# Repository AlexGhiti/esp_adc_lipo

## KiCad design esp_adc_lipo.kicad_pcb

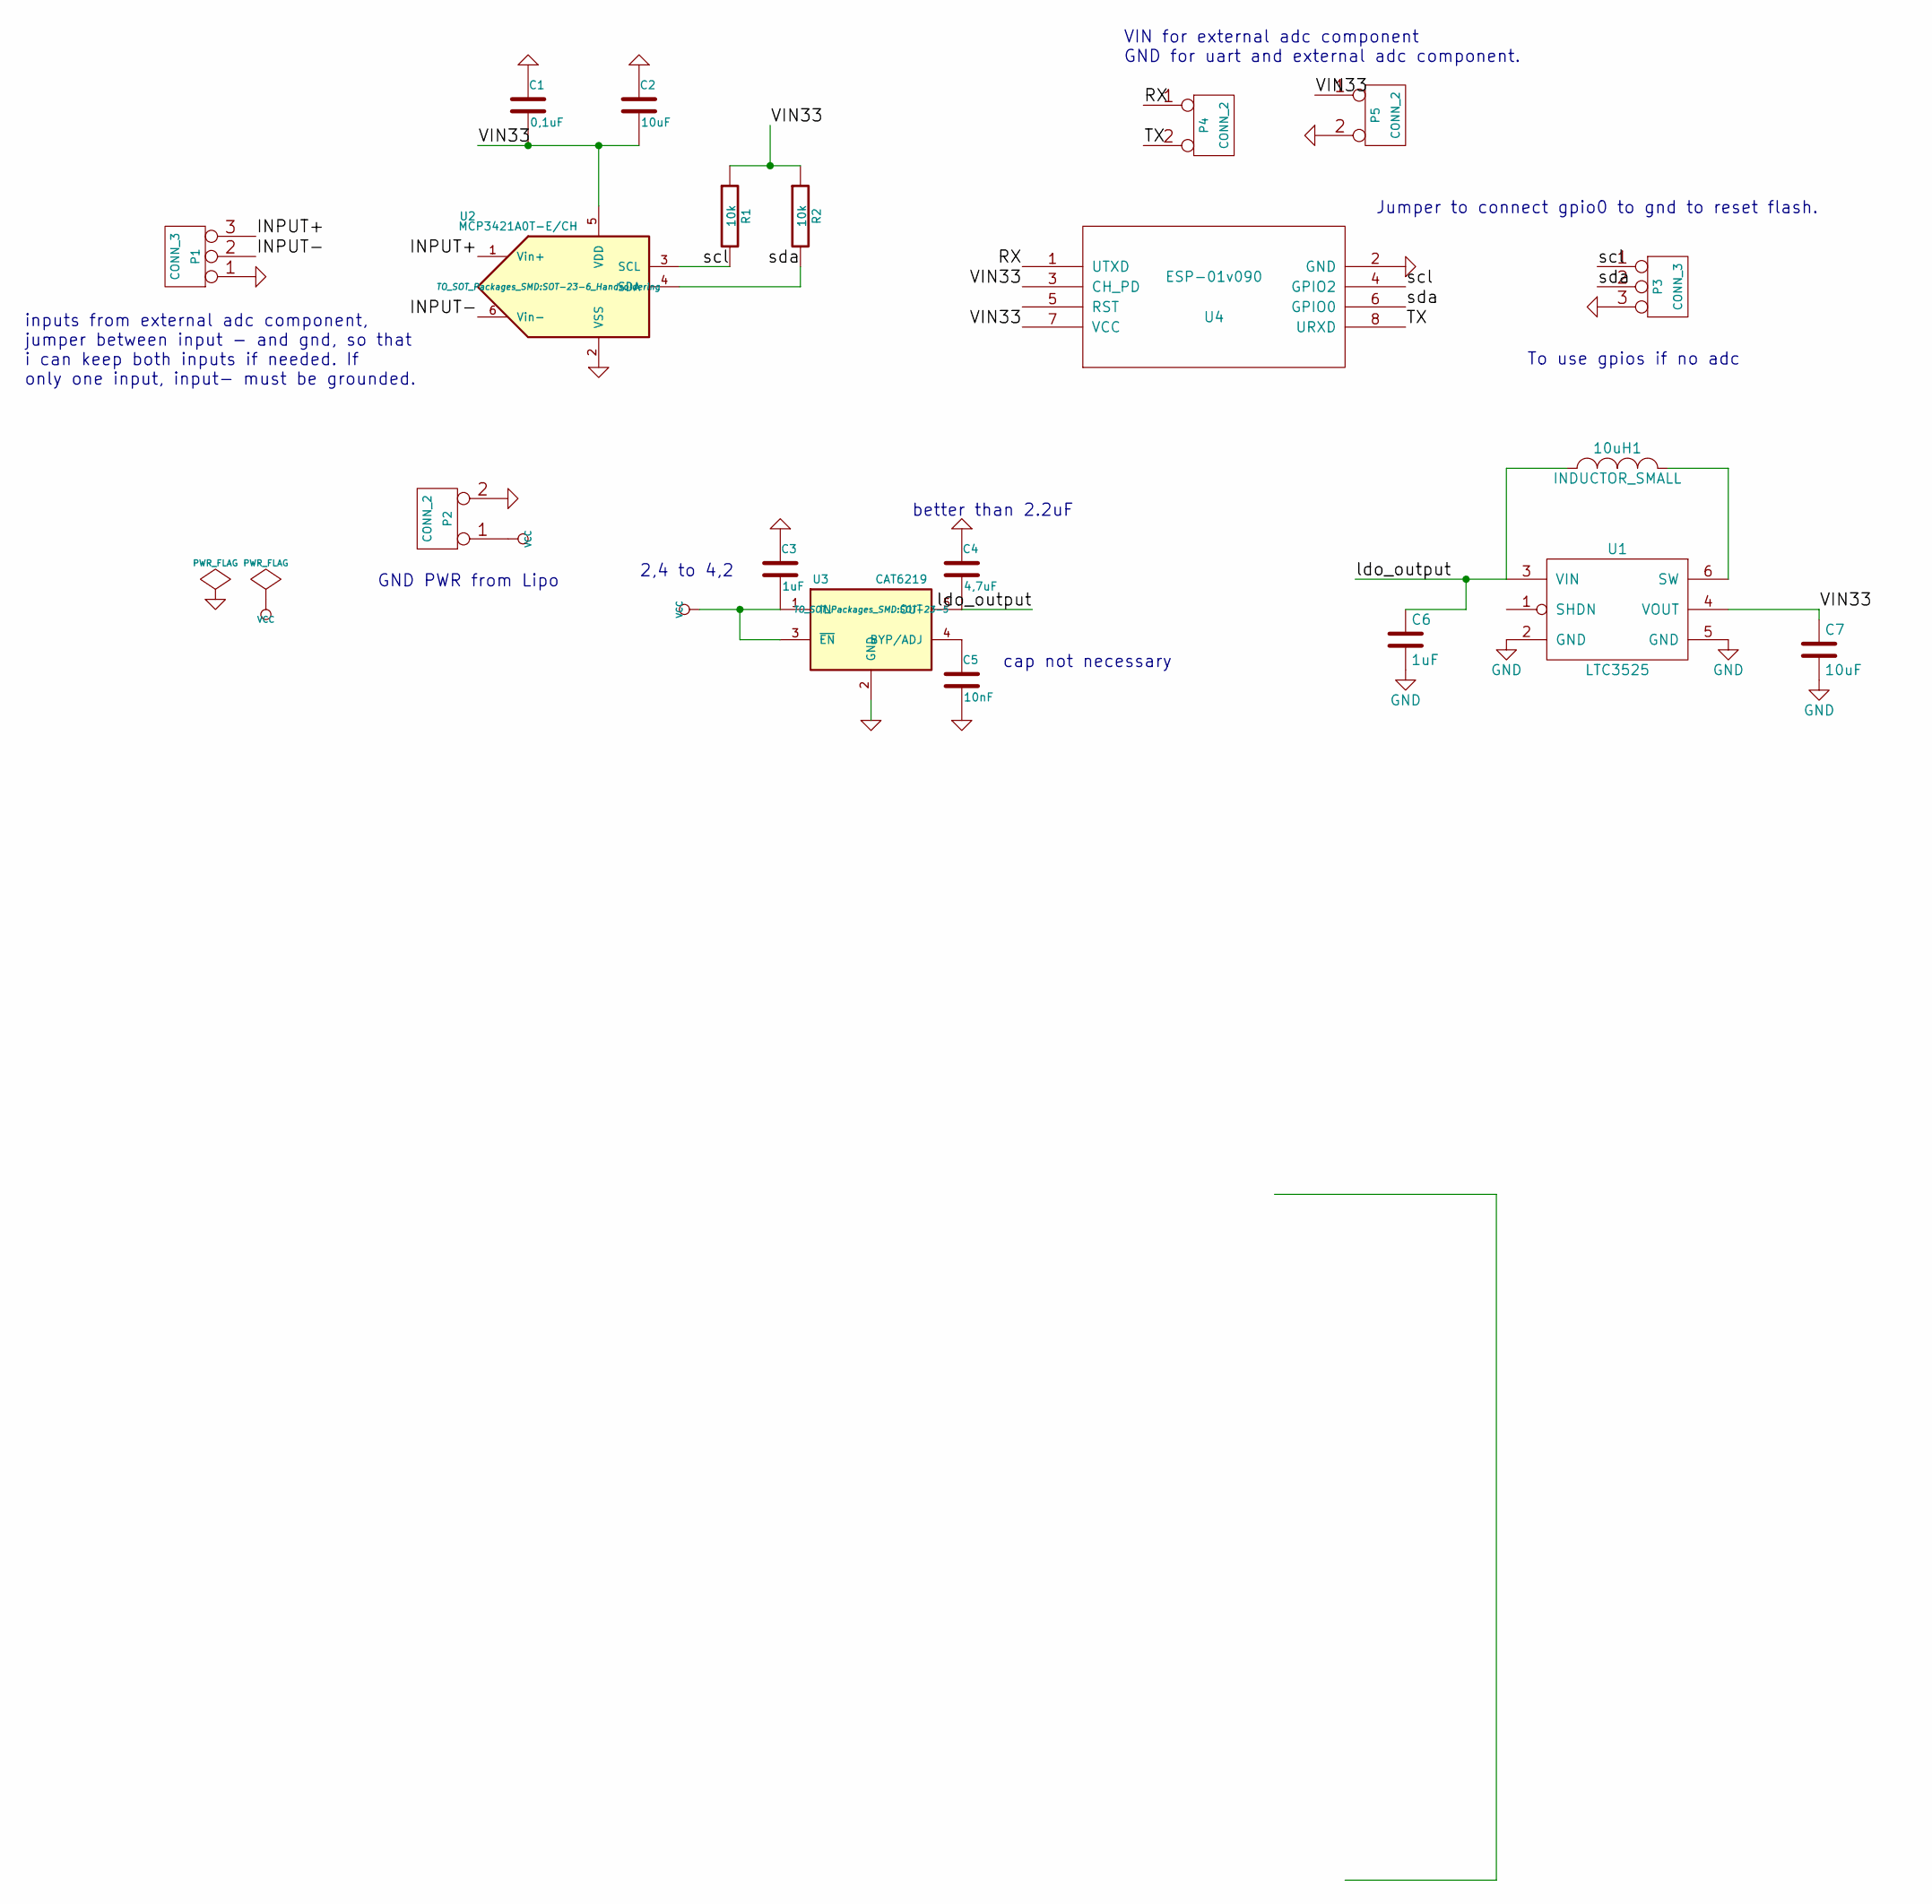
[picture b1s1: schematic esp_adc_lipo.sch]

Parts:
10uH1: INDUCTOR_SMALL; Neosid_Inductor_SM-NE30_SMD1210
C1: 0,1uF; C_0603_HandSoldering
C2, C7: 10uF; C_0603_HandSoldering
C3, C6: 1uF; C_0603_HandSoldering
C4: 4,7uF; C_0603_HandSoldering
C5: 10nF; C_0603_HandSoldering
P1, P3: CONN_3; PINHEAD1-3
P2, P4, P5: CONN_2; PINHEAD1-2
R1, R2: 10k; R_0603_HandSoldering
U1: LTC3525; SC-70-6_Handsoldering
U2: MCP3421A0T-E/CH; SOT-23-6_Handsoldering
U3: CAT6219; SOT-23-5
U4: ESP-01v090; ESP01

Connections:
/INPUT+: P1.3, U2.1 (Vin+)
/INPUT-: P1.2 (PM), U2.6 (Vin-)
/RX: P4.1, U4.1 (UTXD)
/TX: P4.2 (PM), U4.8 (URXD)
/VIN33: C1.2, C2.2, C7.1, P5.1, R1.1, R2.1, U1.4 (VOUT), U2.5 (VDD), U4.3 (CH_PD), U4.7 (VCC)
/ldo_output: 10uH1.1, C4.2, C6.1, U1.3 (VIN), U3.5 (OUT)
/scl: P3.1, R1.2, U2.3 (SCL), U4.4 (GPIO2)
/sda: P3.2 (PM), R2.2, U2.4 (SDA), U4.6 (GPIO0)
GND: C1.1, C2.1, C3.1, C4.1, C5.2, C6.2, C7.2, P1.1, P2.2 (PM), P3.3, P5.2 (PM), U1.2 (GND), U1.5 (GND), U2.2 (VSS), U3.2 (GND), U4.2 (GND)
unnamed: 10uH1.2, U1.6 (SW)
unnamed: C5.1, U3.4 (BYP/ADJ)
VCC: C3.2, P2.1, U3.1 (IN), U3.3 (~EN~)

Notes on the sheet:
2,4 to 4,2
better than 2.2uF
cap not necessary
GND PWR from Lipo
inputs from external adc component, jumper between input - and gnd, so that i can keep both inputs if needed. If only one input, input- must be grounded.
Jumper to connect gpio0 to gnd to reset flash.
To use gpios if no adc
VIN for external adc component GND for uart and external adc component.

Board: 2 copper layers, 19 parts (0 on the bottom side), 12 nets, no tracks yet.

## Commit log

2017-06-18 esp_adc_lipo: Commit functional version.
    Used for temperature sensor => allows ~4months of autonomy.
